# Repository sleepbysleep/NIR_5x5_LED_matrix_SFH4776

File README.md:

# NIR_5x5_LED_matrix_SFH4776
5x5 LED matrix of SFH4776 and GW CSSRM2.CM ranging in Vis/Nir

#

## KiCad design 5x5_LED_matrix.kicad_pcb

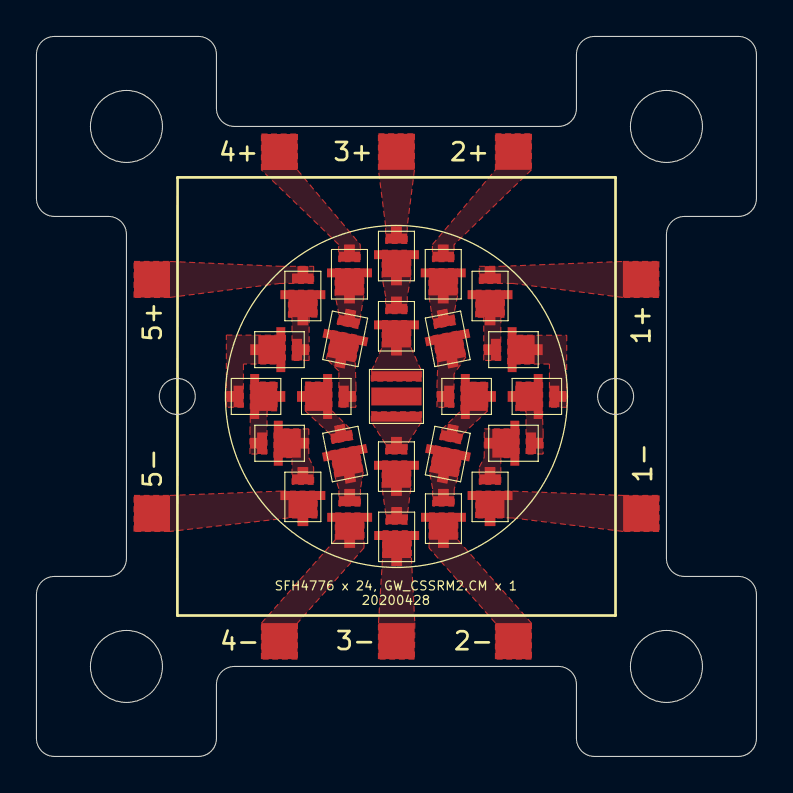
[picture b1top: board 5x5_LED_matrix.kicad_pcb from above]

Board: 2 copper layers, 40.0 x 40.0 mm, 35 parts (0 on the bottom side), 30 nets, no tracks yet.

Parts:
1+, 2+, 3+, 4+, 5+: +; SMD_1P_2.8x2.0
1-, 2-, 3-, 4-, 5-: -; SMD_1P_2.8x2.0
D1, D2, D3, D4, D5, D6, D7, D8, D9, D10, D11, D15, D16, D17, D18, D19, D20, D21, D22, D23, D24, D25: SFH4776; LED-SFH4776_OSRAM_fit
D12, D14: GW_CSSRM2.CM; LED-SFH4776_OSRAM_fit
D13: GW_CSSRM2.CM; LED-GWCSSRM2.CM_OSRAM

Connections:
unnamed: D1.1, D2.2
unnamed: 1+.1, D1.2
unnamed: D2.1, D3.2
unnamed: D3.1, D4.2
unnamed: D4.1, D5.2
unnamed: 1-.1, D5.1
unnamed: D6.1, D7.2
unnamed: 2+.1, D6.2
unnamed: D7.1, D8.2
unnamed: D8.1, D9.2
unnamed: 2-.1, D10.1
unnamed: D9.1, D10.2
unnamed: D11.1, D12.2
unnamed: 3+.1, D11.2
unnamed: D12.1, D13.2
unnamed: D13.1, D14.2
unnamed: D14.1, D15.2
unnamed: 3-.1, D15.1
unnamed: D16.1, D17.2
unnamed: 4+.1, D16.2
unnamed: D17.1, D18.2
unnamed: D18.1, D19.2
unnamed: D19.1, D20.2
unnamed: 4-.1, D20.1
unnamed: D21.1, D22.2
unnamed: 5+.1, D21.2
unnamed: D22.1, D23.2
unnamed: D23.1, D24.2
unnamed: D24.1, D25.2
unnamed: 5-.1, D25.1

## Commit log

2020-08-21 Major change close to final.
